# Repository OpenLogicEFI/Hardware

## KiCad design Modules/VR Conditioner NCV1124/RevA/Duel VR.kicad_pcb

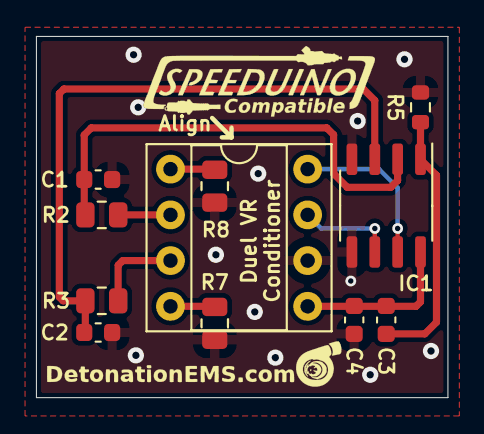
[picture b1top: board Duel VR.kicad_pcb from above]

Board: 2 copper layers, 22.9 x 20.1 mm, 13 parts (0 on the bottom side), 11 nets.

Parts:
C1, C2, C3: 22nF; C_0603_1608Metric
C4: 220nF; C_0603_1608Metric
G1: Logo_Open_Hardware_Small; SpeeduinoCompatible-14mm
G2: Logo_Open_Hardware_Small; DetonationEMS-17mm
IC1: NCV1124; SO-8_3.9x4.9mm_P1.27mm
J1: Speedy VR Mount; DIP-8_W7.62mm_Socket_VRConditioner
R2, R3: 16k; R_0805_2012Metric
R5: 18k; R_0603_1608Metric
R7, R8: 1k; R_0805_2012Metric

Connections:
GND: C1.1, C2.2, C4.2, IC1.4 (GND), IC1.5 (DIAG), J1.6, R5.1, R7.2, R8.2
unnamed: C1.2, IC1.2 (IN1), R2.1
unnamed: C2.1, IC1.3 (IN2), R3.1
unnamed: C3.1, IC1.1 (INadj), R5.2
VDD: C3.2, C4.1, IC1.8 (VCC), J1.5
VR1+: J1.2, R2.2
VR1-: J1.1, R8.1
VR1OUT: IC1.7 (OUT1), J1.8
VR2+: J1.3, R3.2
VR2-: J1.4, R7.1
VR2OUT: IC1.6 (OUT2), J1.7
